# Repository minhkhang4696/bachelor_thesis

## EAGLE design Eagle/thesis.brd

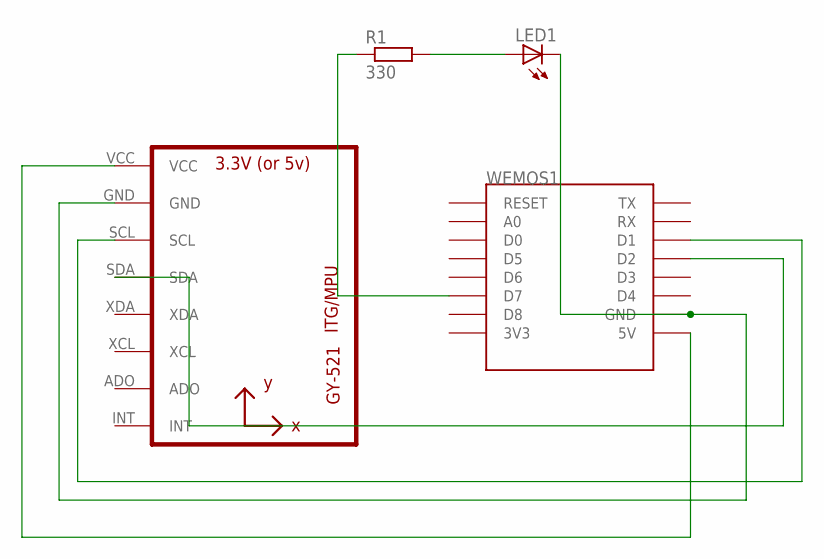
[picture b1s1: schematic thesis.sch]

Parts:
LED1: LED3MM
R1: 330; 0204/7
U1: GY-521MPU6050; GY-521
WEMOS1: WEMOS-D1-MINI

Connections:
unnamed: U1.VCC, WEMOS1.5V
unnamed: LED1.K (C), U1.GND, WEMOS1.GND
unnamed: U1.SCL, WEMOS1.D1
unnamed: U1.SDA, WEMOS1.D2
unnamed: R1.1, WEMOS1.D7
unnamed: LED1.A, R1.2

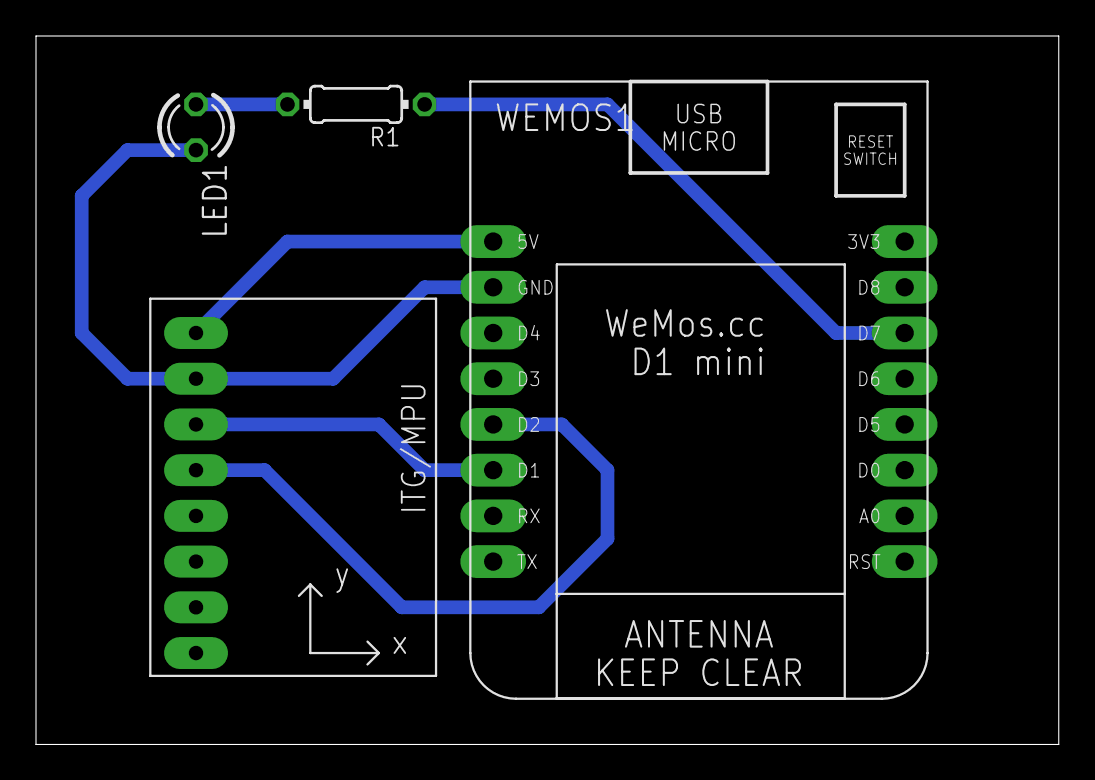
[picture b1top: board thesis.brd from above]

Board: 2 copper layers, 56.8 x 39.4 mm, 4 parts (0 on the bottom side), 6 nets.

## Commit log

2018-07-12 Thesis_code
    First commit
2018-07-12 change lowAcc
2018-07-12 change highAcc
2018-07-12 library
2018-07-12 Add callback for Asyncclient
    Add callback functions for Asyncclient
    Add debugPrint function
2018-07-12 add indicator pin
2018-07-12 beautifier
2018-07-12 beautifier do ngu hon
2018-07-24 thesis document
2018-07-25 eagle-design-and-continue-thesis
2018-07-30 commit 30/7 22:30
2018-07-30 end of 30/7
2018-07-31 dim_light_1st
2018-07-31 bad_staircase_design
2018-07-31 31/7 6:10
2018-08-01 editted 1/8
2018-08-01 First_draft_till_economy
2018-08-02 completed chapter 1
2018-08-02 correct_chapter_1
2018-08-03 commercial_device
2018-08-03 tempo_complete
2018-08-03 complete_literature_review
2018-08-06 problem
2018-08-07 position of sensor first draft
2018-08-07 sensor placement second draft
2018-08-09 dang viet do embedded software
    sau khi success connect
2018-08-09 completed embedded software
2018-08-09 complete 9/8
2018-08-14 complete final design image
2018-08-20 first_correction_prof
    chua check lai sau khi sua loi
2018-08-22 complete 4/6 data table
2018-08-23 add new data of ADLs
2018-08-23 adding figure ADLs
2018-08-30 30/8/2018 morning
2018-08-30 chieu 30/8
2018-09-02 still have comparison and futurework
2018-09-03 con so sanh
2018-09-03 con compare la xong
2018-09-08 Final Correction
2018-09-17 ppt edit
2018-09-18 ppt editted 2
2018-09-18 ppt complete
2026-03-31 Add initial content to README.md
